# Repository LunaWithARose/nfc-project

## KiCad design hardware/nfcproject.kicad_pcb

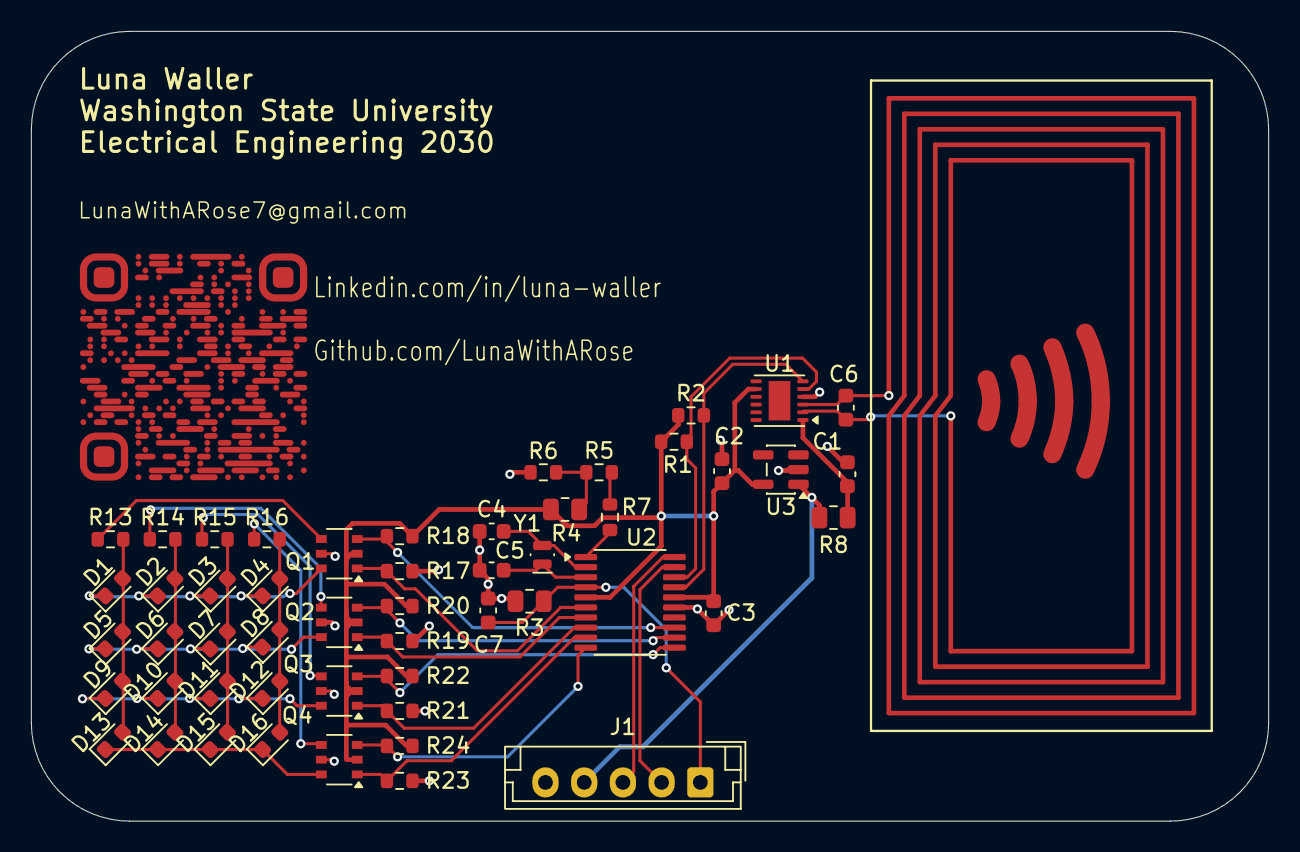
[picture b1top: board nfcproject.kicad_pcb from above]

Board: 2 copper layers, 79.9 x 51.0 mm, 53 parts (0 on the bottom side), 35 nets.

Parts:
C1, C2: 1u; C_0603_1608Metric
C3, C7: 100n; C_0603_1608Metric
C4, C5: 8pf; C_0603_1608Metric
C6: 82pf; C_0603_1608Metric
D1, D2, D3, D4, D5, D6, D7, D8, D9, D10, D11, D12, D13, D14, D15, D16: LED; LED_0603_1608Metric
J1: Conn_01x05_Pin; JST_EH_B5B-EH-A_1x05_P2.50mm_Vertical
L1: NFC; nfc_ant
Q1, Q2, Q3, Q4: TSOP-6_1.65x3.05mm_P0.95mm
R1, R2, R5, R6, R7: 4K7; R_0603_1608Metric
R3, R4, R8: R; R_0805_2012Metric
R13, R14, R15, R16: 470; R_0603_1608Metric
R17, R18, R19, R20, R21, R22, R23, R24: 50K; R_0603_1608Metric
U1: ST25DV04K-IER8C3; ST_UFDFPN-12-1EP_3x3mm_P0.5mm_EP1.4x2.55mm
U2: STM32L010F4Px; TSSOP-20_4.4x6.5mm_P0.65mm
U3: TPS7A0508PDBV; SOT-23-5
Y1: 32.786 Mhz; Crystal_SMD_MicroCrystal_CM9V-T1A-2Pin_1.6x1.0mm

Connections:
+2V5: C2.2, C3.2, Q1.2, Q2.2, Q3.2, Q4.2, R1.1, R2.1, R4.1, R18.2, R20.2, R22.2, R24.2, U1.8 (VCC), U2.5 (VDDA), U2.16 (VDD), U3.5 (OUT)
/1: D1.1 (K), D2.1 (K), D3.1 (K), D4.1 (K), Q1.6
/2: D5.1 (K), D6.1 (K), D7.1 (K), D8.1 (K), Q2.6
/3: D9.1 (K), D10.1 (K), D11.1 (K), D12.1 (K), Q3.6
/4: D13.1 (K), D14.1 (K), D15.1 (K), D16.1 (K), Q4.6
/A: Q1.4, R13.1
/B: Q2.4, R14.1
/C: Q3.4, R15.1
/D: Q4.4, R16.1
/N1: Q1.1, R17.1, U2.6 (PA0)
/N2: Q2.1, R19.1, U2.7 (PA1)
/N3: Q3.1, R21.1, U2.8 (PA2)
/N4: Q4.1, R23.1, U2.9 (PA3)
/NRST: C7.2, J1.1, R3.2, U2.4 (NRST)
/P1: Q1.3, R18.1, U2.13 (PA7)
/P2: Q2.3, R20.1, U2.12 (PA6)
/P3: Q3.3, R22.1, U2.11 (PA5)
/P4: Q4.3, R24.1, U2.10 (PA4)
/SCL: R2.2, U1.6 (SCL), U2.17 (PA9)
/SDA: R1.2, U1.5 (SDA), U2.18 (PA10)
/SWCLK: J1.3, U2.20 (PA14)
/SWDIO: J1.2, U2.19 (PA13)
GND: C1.1, C2.1, C3.1, C4.1, C5.1, C7.1, J1.5, Q1.5, Q2.5, Q3.5, Q4.5, R3.1, R6.2, R17.2, R19.2, R21.2, R23.2, U1.4 (VSS), U2.15 (VSS), U3.2 (GND)
unnamed: D1.2 (A), D5.2 (A), D9.2 (A), D13.2 (A), R13.2
unnamed: D2.2 (A), D6.2 (A), D10.2 (A), D14.2 (A), R14.2
unnamed: D3.2 (A), D7.2 (A), D11.2 (A), D15.2 (A), R15.2
unnamed: D4.2 (A), D8.2 (A), D12.2 (A), D16.2 (A), R16.2
unnamed: R4.2, R5.2, R6.1
unnamed: R5.1, R7.2
unnamed: C6.1, C6.2, L1.1, L1.2, U1.2 (AC0), U1.3 (AC1)
unnamed: C1.2, R8.2, U1.1 (V_EH)
unnamed: R7.1, U2.1 (PB9)
unnamed: C4.2, U2.2 (PC14), Y1.2
unnamed: C5.2, U2.3 (PC15), Y1.1
VCC: J1.4, R8.1, U3.1 (IN)
